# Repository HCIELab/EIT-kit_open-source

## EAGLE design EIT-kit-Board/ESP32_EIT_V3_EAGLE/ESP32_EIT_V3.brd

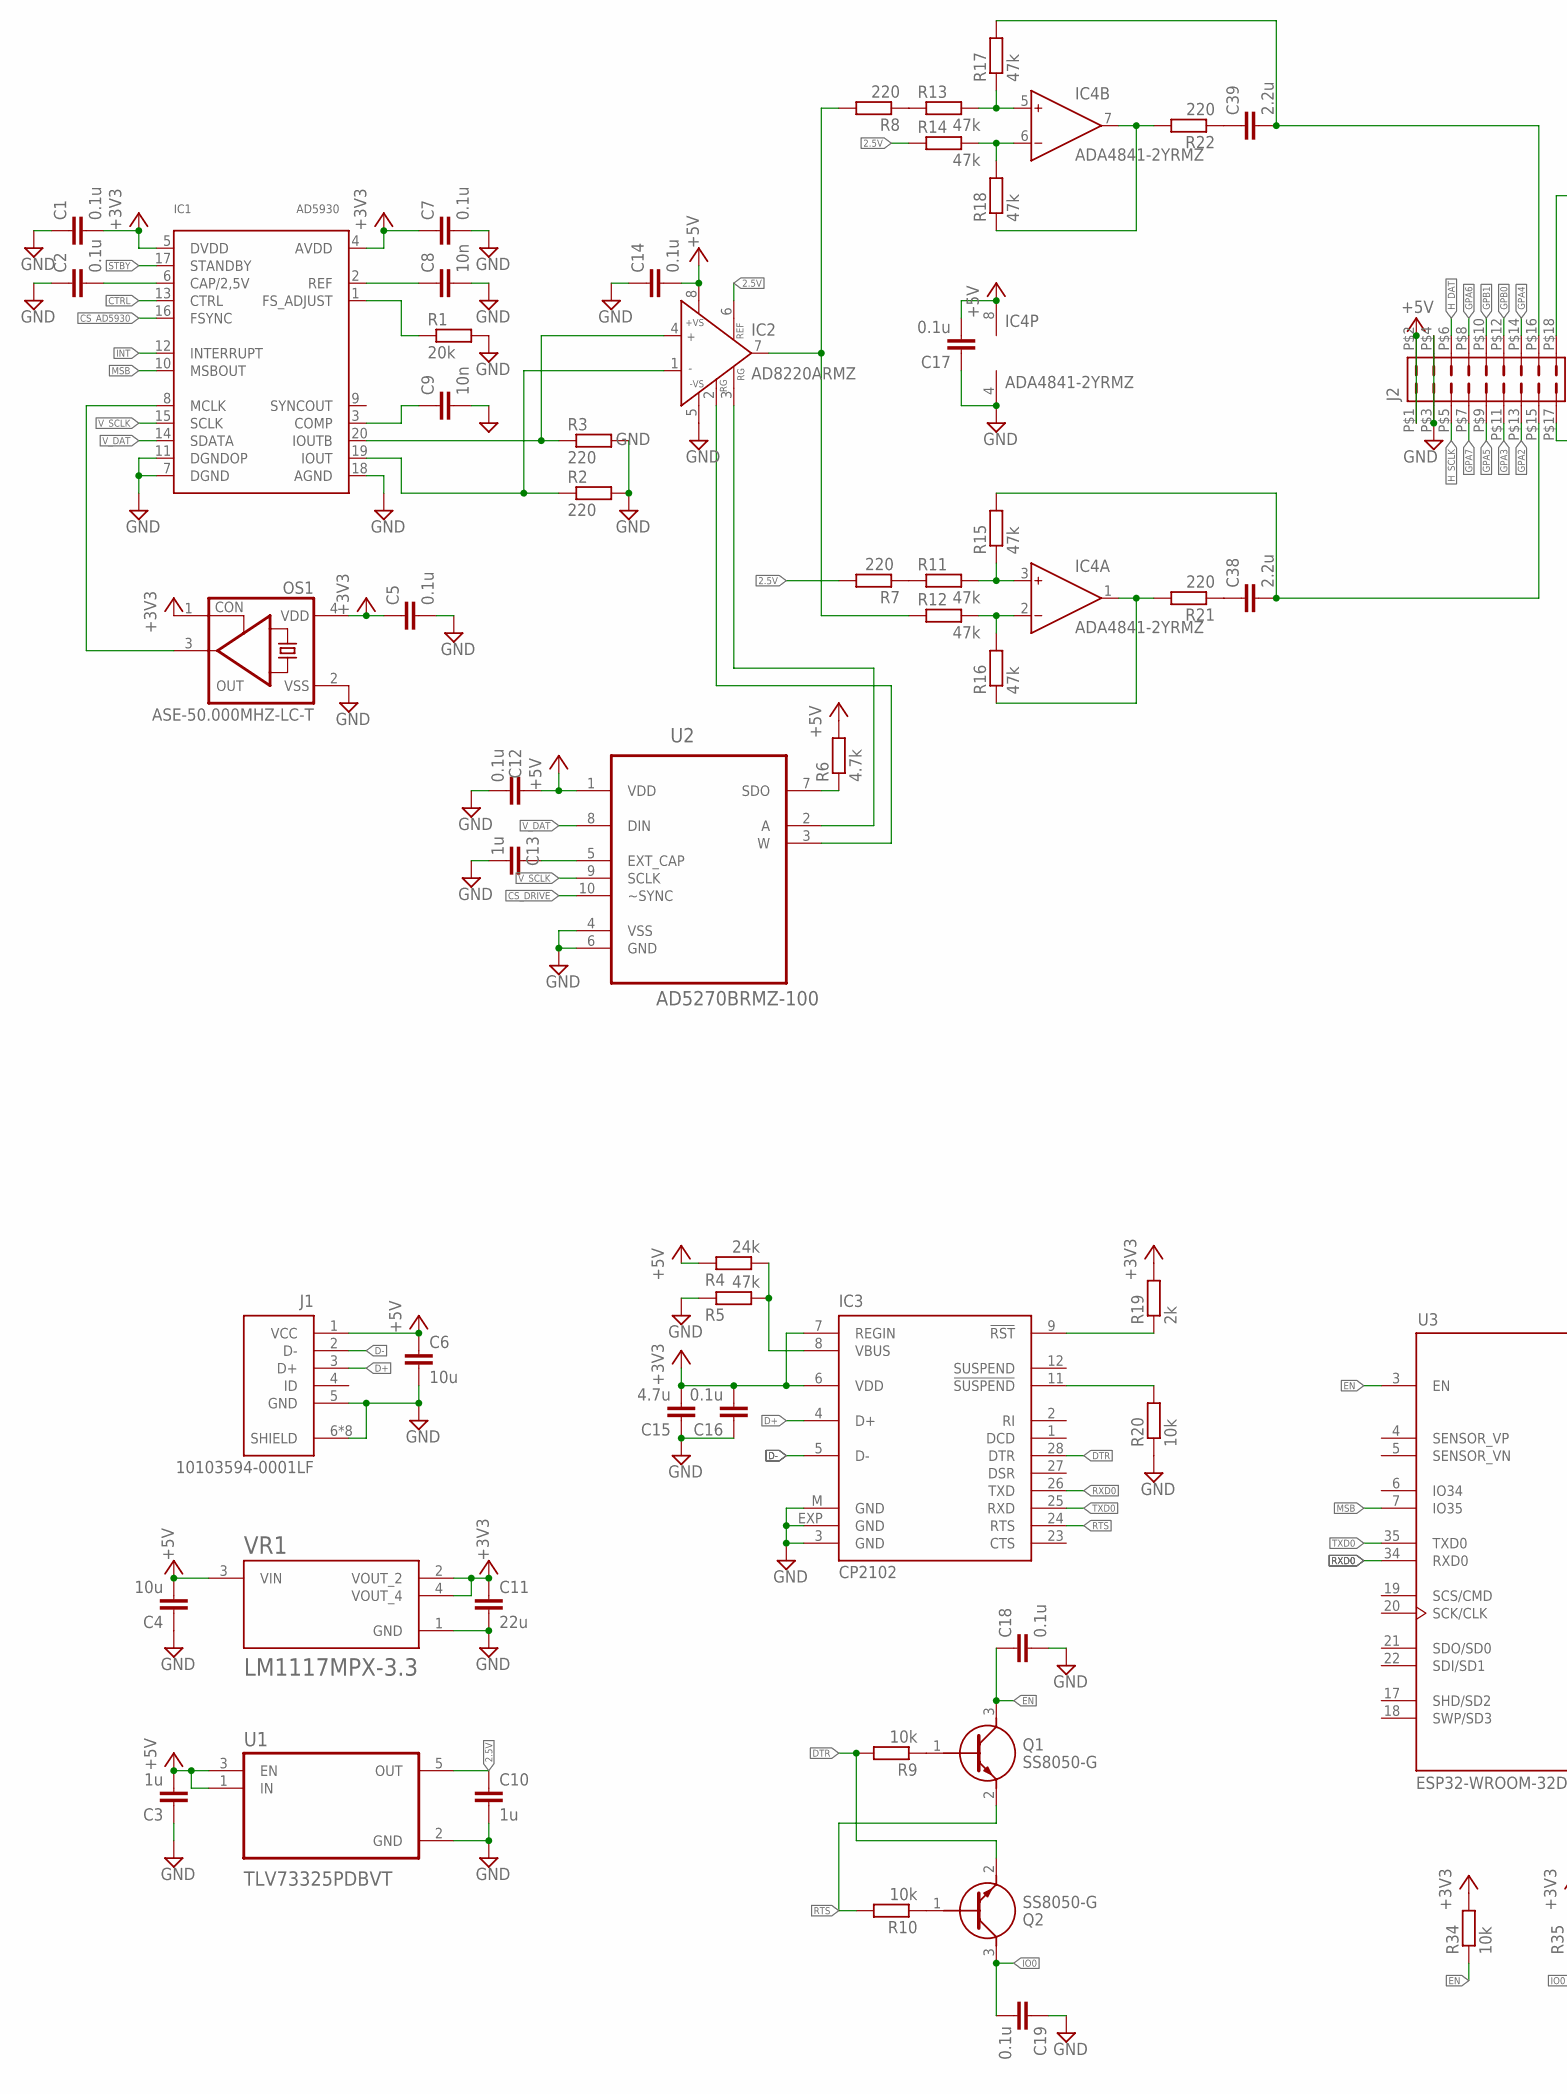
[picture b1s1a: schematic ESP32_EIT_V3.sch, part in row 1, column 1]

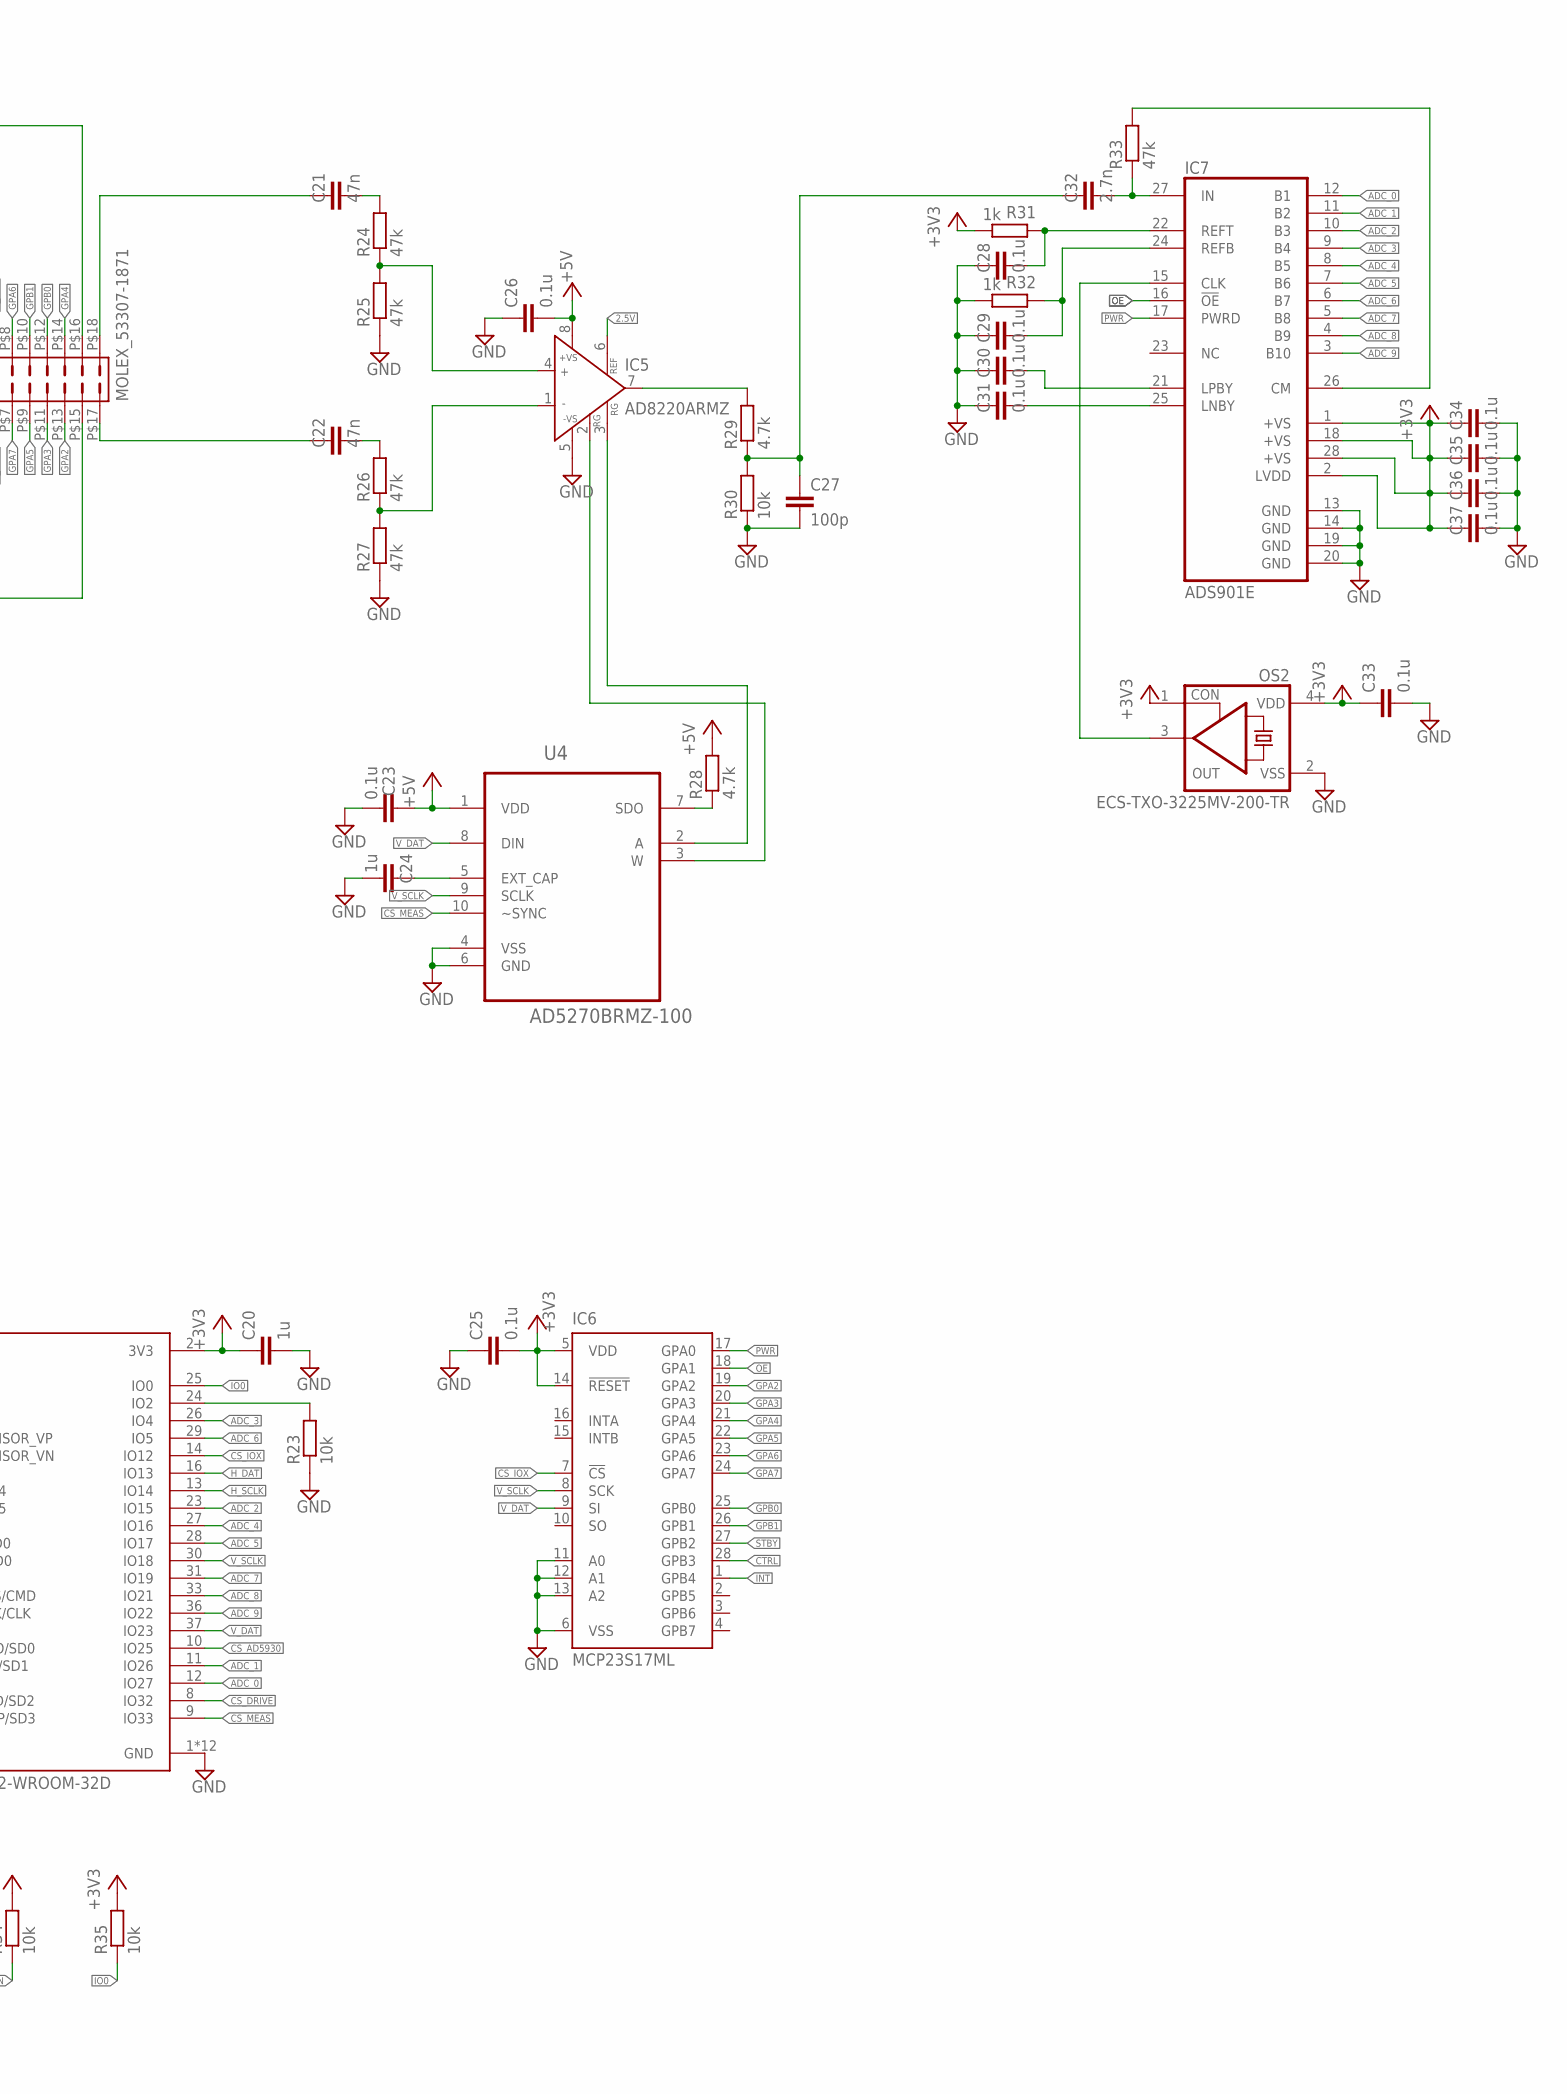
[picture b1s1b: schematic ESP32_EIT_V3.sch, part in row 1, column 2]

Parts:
C1, C2, C5, C7, C12, C14, C16, C17, C18, C19, C23, C25, C26, C28, C29, C30, C31, C33, C34, C35, C36, C37: 0.1u; C0603
C3, C10, C13, C20, C24: 1u; C0603
C4, C6: 10u; C0805
C8, C9: 10n; C0603
C11: 22u; C0805
C15: 4.7u; C0603
C21, C22: 47n; C0603
C27: 100p; C0603
C32: 2.7n; C0603
C38, C39: 2.2u; C0603
IC1: AD5930; TSSOP20
IC2, IC5: AD8220ARMZ; MSOP8
IC3: CP2102; MLP28
IC4: ADA4841-2YRMZ; MSOP8
IC6: MCP23S17ML; QFN28-ML_6X6MM
IC7: ADS901E; SSOP28BU
J1: 10103594-0001LF; AMPHENOL_10103594-0001LF
J2: MOLEX_53307-1871
OS1: ASE-50.000MHZ-LC-T; 2.5X2-4-PAD
OS2: ECS-TXO-3225MV-200-TR; 2.5X2-4-PAD
Q1, Q2: SS8050-G; SOT95P240X115-3N
R1: 20k; R0603
R2, R3, R7, R8, R21, R22: 220; R0603
R4: 24k; R0603
R5, R11, R12, R13, R14, R15, R16, R17, R18, R24, R25, R26, R27, R33: 47k; R0603
R6, R28, R29: 4.7k; R0603
R9, R10, R20, R23, R30, R34, R35: 10k; R0603
R19: 2k; R0603
R31, R32: 1k; R0603
U1: TLV73325PDBVT; SOT95P280X145-5N
U2, U4: AD5270BRMZ-100; SOP50P490X110-10N
U3: ESP32-WROOM-32D; MODULE_ESP32-WROOM-32D
VR1: LM1117MPX-3.3; VREG_LM1117MPX-3.3

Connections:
2.5V: C10.1, IC2.6 (REF), IC5.6 (REF), R7.2, R14.1, U1.5 (OUT)
+3V3: C1.2, C5.1, C7.1, C11.1, C15.2, C16.2, C20.1, C25.2, C33.1, C34.1, C35.1, C36.1, C37.1, IC1.4 (AVDD), IC1.5 (DVDD), IC3.6 (VDD), IC3.7 (REGIN), IC6.5 (VDD), IC6.14 (!RESET), IC7.1 (+VS), IC7.2 (LVDD), IC7.18 (+VS), IC7.28 (+VS), OS1.1 (CON), OS1.4 (VDD), OS2.1 (CON), OS2.4 (VDD), R19.2, R31.2, R34.2, R35.2, U3.2 (3V3), VR1.2 (VOUT_2), VR1.4 (VOUT_4)
+5V: C3.2, C4.2, C6.1, C12.1, C14.2, C17.2, C23.1, C26.2, IC2.8 (+VS), IC4.8 (V+), IC5.8 (+VS), J1.1 (VCC), J2.P$1 (1), J2.P$2 (2), R4.2, R6.2, R28.2, U1.1 (IN), U1.3 (EN), U2.1 (VDD), U4.1 (VDD), VR1.3 (VIN)
ADC_0: IC7.12 (B1), U3.12 (IO27)
ADC_1: IC7.11 (B2), U3.11 (IO26)
ADC_2: IC7.10 (B3), U3.23 (IO15)
ADC_3: IC7.9 (B4), U3.26 (IO4)
ADC_4: IC7.8 (B5), U3.27 (IO16)
ADC_5: IC7.7 (B6), U3.28 (IO17)
ADC_6: IC7.6 (B7), U3.29 (IO5)
ADC_7: IC7.5 (B8), U3.31 (IO19)
ADC_8: IC7.4 (B9), U3.33 (IO21)
ADC_9: IC7.3 (B10), U3.36 (IO22)
CS_AD5930: IC1.16 (FSYNC), U3.10 (IO25)
CS_DRIVE: U2.10 (~SYNC), U3.8 (IO32)
CS_IOX: IC6.7 (!CS), U3.14 (IO12)
CS_MEAS: U3.9 (IO33), U4.10 (~SYNC)
CTRL: IC1.13 (CTRL), IC6.28 (GPB3)
D+: IC3.4 (D+), J1.3 (D+)
D-: IC3.5 (D-), J1.2 (D-)
DTR: IC3.28 (DTR), Q2.2 (E), R9.2
EN: C18.1, Q1.3 (C), R34.1, U3.3 (EN)
GND: C1.1, C2.1, C3.1, C4.1, C5.2, C6.2, C7.2, C8.2, C9.2, C10.2, C11.2, C12.2, C13.2, C14.1, C15.1, C16.1, C17.1, C18.2, C19.1, C20.2, C23.2, C24.2, C25.1, C26.1, C27.2, C28.1, C29.1, C30.1, C31.1, C33.2, C34.2, C35.2, C36.2, C37.2, IC1.7 (DGND), IC1.11 (DGNDOP), IC1.18 (AGND), IC2.5 (-VS), IC3.3 (GND), IC3.EXP (GND), IC3.M (GND), IC4.4 (V-), IC5.5 (-VS), IC6.6 (VSS), IC6.11 (A0), IC6.12 (A1), IC6.13 (A2), IC7.13 (GND), IC7.14 (GND), IC7.19 (GND), IC7.20 (GND), J1.5 (GND), J1.6 (SHIELD), J1.7 (SHIELD), J1.8 (SHIELD), J1.9 (SHIELD), J1.10 (SHIELD), J1.11 (SHIELD), J1.S1 (SHIELD), J1.S2 (SHIELD), J2.P$3 (3), J2.P$4 (4), OS1.2 (VSS), OS2.2 (VSS), R1.2, R2.2, R3.2, R5.2, R20.1, R23.1, R25.1, R27.1, R30.1, R32.2, U1.2 (GND), U2.4 (VSS), U2.6 (GND), U3.1 (GND), U3.15 (GND), U3.38 (GND), U3.39_1 (GND), U3.39_2 (GND), U3.39_3 (GND), U3.39_4 (GND), U3.39_5 (GND), U3.39_6 (GND), U3.39_7 (GND), U3.39_8 (GND), U3.39_9 (GND), U4.4 (VSS), U4.6 (GND), VR1.1 (GND)
GPA2: IC6.19 (GPA2), J2.P$13 (13)
GPA3: IC6.20 (GPA3), J2.P$11 (11)
GPA4: IC6.21 (GPA4), J2.P$14 (14)
GPA5: IC6.22 (GPA5), J2.P$9 (9)
GPA6: IC6.23 (GPA6), J2.P$8 (8)
GPA7: IC6.24 (GPA7), J2.P$7 (7)
GPB0: IC6.25 (GPB0), J2.P$12 (12)
GPB1: IC6.26 (GPB1), J2.P$10 (10)
H_DAT: J2.P$6 (6), U3.16 (IO13)
H_SCLK: J2.P$5 (5), U3.13 (IO14)
INT: IC1.12 (INTERRUPT), IC6.1 (GPB4)
IO0: C19.2, Q2.3 (C), R35.1, U3.25 (IO0)
MSB: IC1.10 (MSBOUT), U3.7 (IO35)
unnamed: IC1.1 (FS_ADJUST), R1.1
unnamed: C8.1, IC1.2 (REF)
unnamed: C9.1, IC1.3 (COMP)
unnamed: IC1.20 (IOUTB), IC2.4 (IN+), R3.1
unnamed: R7.1, R11.1
unnamed: R8.1, R13.1
unnamed: IC4.6 (IN-), R14.2, R18.2
unnamed: IC4.5 (IN+), R13.2, R17.1
unnamed: IC4.3 (IN+), R11.2, R15.1
unnamed: IC4.2 (IN-), R12.2, R16.2
unnamed: IC4.1 (OUT), R16.1, R21.2
unnamed: IC1.8 (MCLK), OS1.3 (OUT)
unnamed: C2.2, IC1.6 (CAP/2,5V)
unnamed: IC4.7 (OUT), R18.1, R22.2
unnamed: R6.1, U2.7 (SDO)
unnamed: IC1.19 (IOUT), IC2.1 (IN-), R2.1
unnamed: IC2.2 (RG), U2.3 (W)
unnamed: IC2.7 (OUT), R8.2, R12.1
unnamed: IC2.3 (RG), U2.2 (A)
unnamed: C13.1, U2.5 (EXT_CAP)
unnamed: R28.1, U4.7 (SDO)
unnamed: IC7.26 (CM), R33.2
unnamed: C32.2, IC7.27 (IN), R33.1
unnamed: C24.1, U4.5 (EXT_CAP)
unnamed: C28.2, IC7.22 (REFT), R31.1
unnamed: C29.2, IC7.24 (REFB), R32.1
unnamed: C31.2, IC7.25 (LNBY)
unnamed: C30.2, IC7.21 (LPBY)
unnamed: IC5.2 (RG), U4.3 (W)
unnamed: IC7.15 (CLK), OS2.3 (OUT)
unnamed: IC5.7 (OUT), R29.2
unnamed: C21.2, R24.2
unnamed: IC5.4 (IN+), R24.1, R25.2
unnamed: IC5.1 (IN-), R26.1, R27.2
unnamed: C22.2, R26.2
unnamed: IC5.3 (RG), U4.2 (A)
unnamed: C27.1, C32.1, R29.1, R30.2
unnamed: IC3.11 (!SUSPEND), R20.2
unnamed: IC3.8 (VBUS), R4.1, R5.1
unnamed: R23.2, U3.24 (IO2)
unnamed: IC3.9 (!RST), R19.1
unnamed: Q1.1 (B), R9.1
unnamed: Q2.1 (B), R10.1
unnamed: C21.1, J2.P$18 (18)
unnamed: C22.1, J2.P$17 (17)
unnamed: C38.2, J2.P$15 (15), R15.2
unnamed: C39.2, J2.P$16 (16), R17.2
unnamed: C38.1, R21.1
unnamed: C39.1, R22.1
OE: IC6.18 (GPA1), IC7.16 (!OE)
PWR: IC6.17 (GPA0), IC7.17 (PWRD)
RTS: IC3.24 (RTS), Q1.2 (E), R10.2
RXD0: IC3.26 (TXD), U3.34 (RXD0)
STBY: IC1.17 (STANDBY), IC6.27 (GPB2)
TXD0: IC3.25 (RXD), U3.35 (TXD0)
V_DAT: IC1.14 (SDATA), IC6.9 (SI), U2.8 (DIN), U3.37 (IO23), U4.8 (DIN)
V_SCLK: IC1.15 (SCLK), IC6.8 (SCK), U2.9 (SCLK), U3.30 (IO18), U4.9 (SCLK)

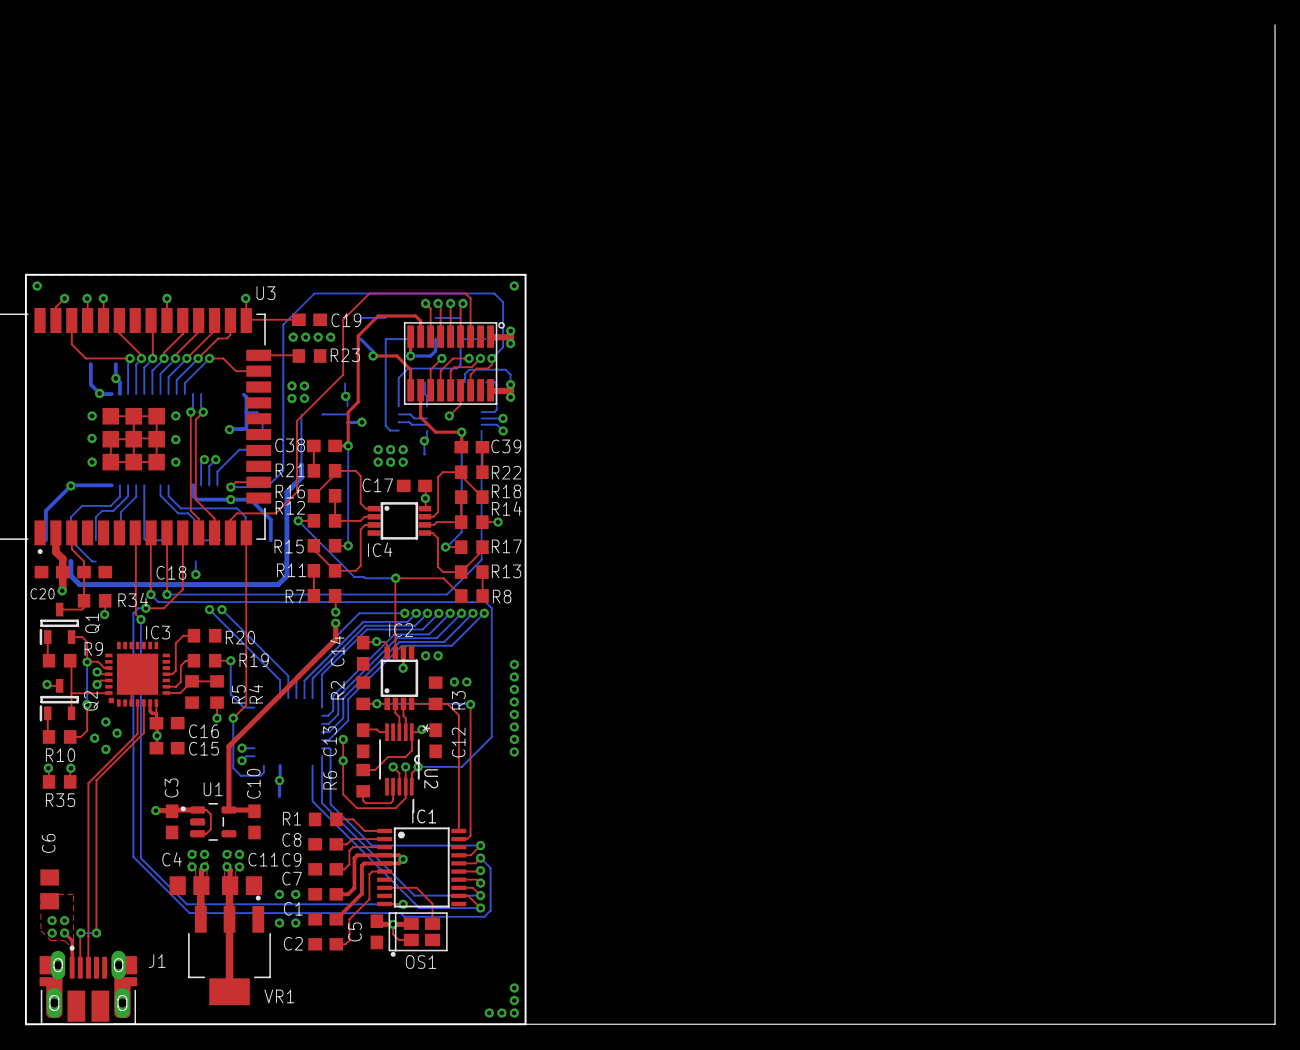
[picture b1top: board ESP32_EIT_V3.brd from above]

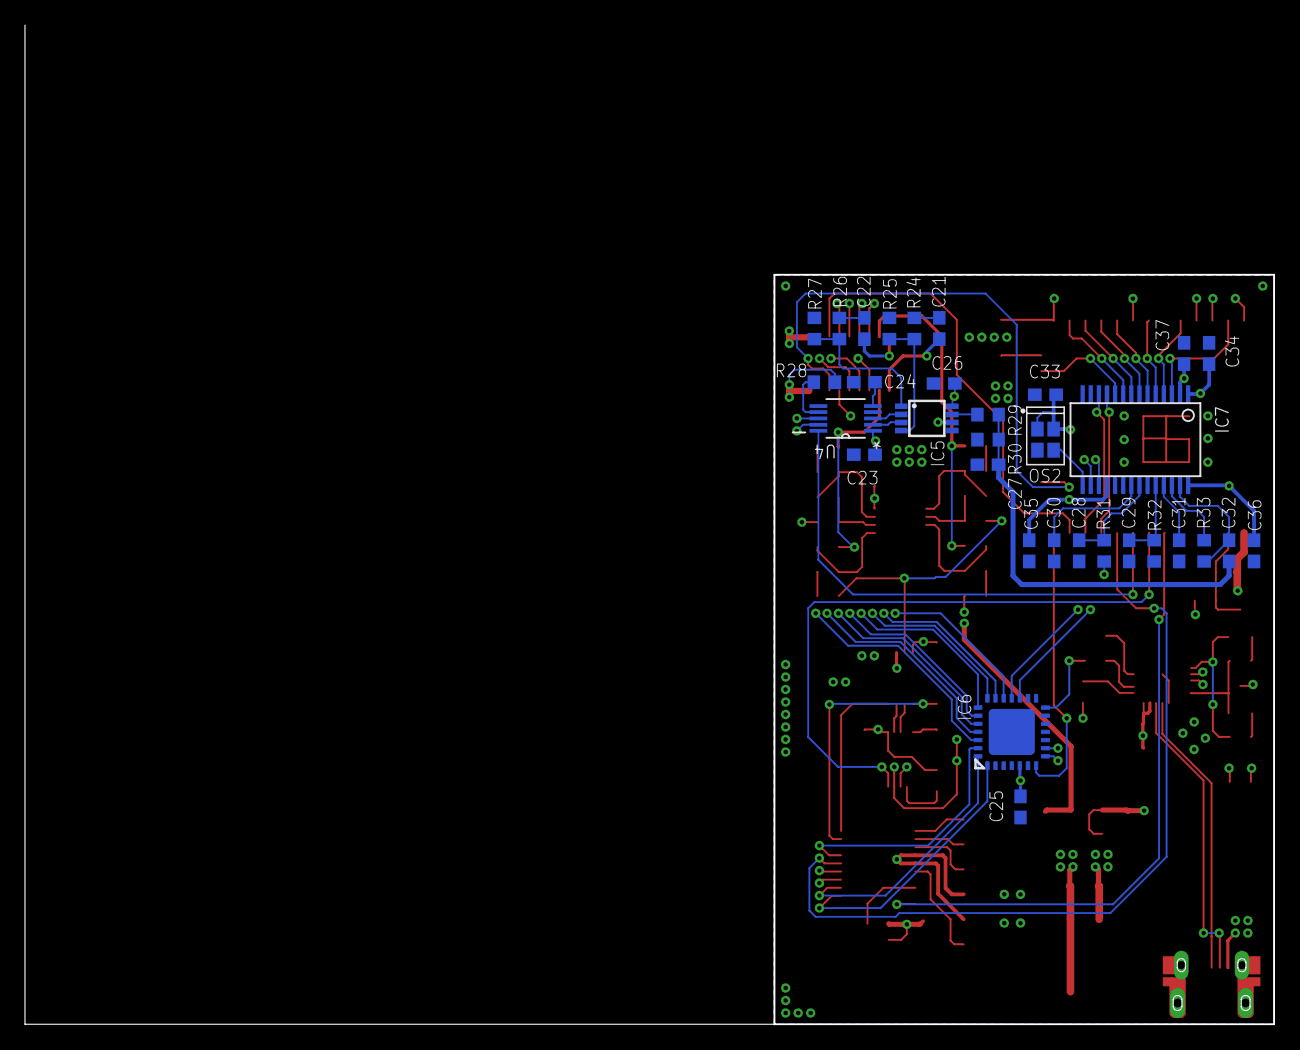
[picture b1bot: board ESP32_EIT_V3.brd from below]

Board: 4 copper layers, 40.0 x 60.0 mm, 92 parts (32 on the bottom side), 93 nets.

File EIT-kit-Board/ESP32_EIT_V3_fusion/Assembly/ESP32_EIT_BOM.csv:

Qty,Value,Device,Package,Parts,Description,
22,0.1u,C-EUC0603,C0603,"C1, C2, C5, C7, C12, C14, C16, C17, C18, C19, C23, C25, C26, C28, C29, C30, C31, C33, C34, C35, C36, C37","CAPACITOR, European symbol",
1,100p,C-EUC0603,C0603,C27,"CAPACITOR, European symbol",
1,10103594-0001LF,10103594-0001LF,AMPHENOL_10103594-0001LF,J1,"USB - micro B USB 2.0 Receptacle Connector 5 Position Surface Mount, Right Angle; Through Hole  Check prices",
7,10k,R-EU_R0603,R0603,"R9, R10, R20, R23, R30, R34, R35","RESISTOR, European symbol",
2,10n,C-EUC0603,C0603,"C8, C9","CAPACITOR, European symbol",
2,10u,C-EUC0805,C0805,"C4, C6","CAPACITOR, European symbol",
2,1k,R-EU_R0603,R0603,"R31, R32","RESISTOR, European symbol",
5,1u,C-EUC0603,C0603,"C3, C10, C13, C20, C24","CAPACITOR, European symbol",
2,2.2u,C-EUC0603,C0603,"C38, C39","CAPACITOR, European symbol",
1,2.7n,C-EUC0603,C0603,C32,"CAPACITOR, European symbol",
1,20k,R-EU_R0603,R0603,R1,"RESISTOR, European symbol",
6,220,R-EU_R0603,R0603,"R2, R3, R7, R8, R21, R22","RESISTOR, European symbol",
1,22u,C-EUC0805,C0805,C11,"CAPACITOR, European symbol",
1,24k,R-EU_R0603,R0603,R4,"RESISTOR, European symbol",
1,2k,R-EU_R0603,R0603,R19,"RESISTOR, European symbol",
3,4.7k,R-EU_R0603,R0603,"R6, R28, R29","RESISTOR, European symbol",
1,4.7u,C-EUC0603,C0603,C15,"CAPACITOR, European symbol",
14,47k,R-EU_R0603,R0603,"R5, R11, R12, R13, R14, R15, R16, R17, R18, R24, R25, R26, R27, R33","RESISTOR, European symbol",
2,47n,C-EUC0603,C0603,"C21, C22","CAPACITOR, European symbol",
2,AD5270BRMZ-100,AD5270BRMZ-100,SOP50P490X110-10N,"U2, U4","1024-/256-Position, 1% Resistor Tolerance Error, SPI Interface and 50-TP Memory Digital Rheostat  Check prices",
1,AD5930,AD5930,TSSOP20,IC1,"Programmable Waveform Generator",
2,AD8220ARMZ,AD8220ARMZ,MSOP8,"IC2, IC5","Single-Supply, Rail-to-Rail, Low Power, FET Input Op Amp",
1,ADA4841-2YRMZ,ADA4841-2YRMZ,MSOP8,IC4,"Ultralow Noise Amplifier at Lower Power",
1,ADS901E,ADS901E,SSOP28BU,IC7,"10-Bit, 20 MSPS ADC SE/Diff Inputs",
1,ASE-50.000MHZ-LC-T,OSC-OE-IQXO-793,2.5X2-4-PAD,OS1,"OSCILLATOR WITH OE",
1,CP2102,CP2102,MLP28,IC3,"Single-Chip USB to UART Bridge",
1,ECS-TXO-3225MV-200-TR,OSC-OE-IQXO-793,2.5X2-4-PAD,OS2,"OSCILLATOR WITH OE",
1,ESP32-WROOM-32D,ESP32-WROOM-32D,MODULE_ESP32-WROOM-32D,U3,"Bluetooth, WiFi 802.11b/g/n, Bluetooth v4.2 + EDR, Class 1, 2 and 3 Transceiver Module 2.4GHz ~ 2.5GHz Integrated, Trace Surface Mount Check prices",
1,LM1117MPX-3.3,LM1117MPX-3.3,VREG_LM1117MPX-3.3,VR1,"800-mA 15-V linear voltage regulator 4-SOT-223 0 to 125  Check prices",
1,MCP23S17ML,MCP23S17ML,QFN28-ML_6X6MM,IC6,http://ww1.microchip.com/downloads/en/DeviceDoc/21952a.pdf,
1,MOLEX_53307-1871,MOLEX_53307-1871,MOLEX_53307-1871,J2,,
2,SS8050-G,SS8050-G,SOT95P240X115-3N,"Q1, Q2","Bipolar Transistors - BJT NPN TRANSISTOR 1.5A 40V",
1,TLV73325PDBVT,TLV73325PDBVT,SOT95P280X145-5N,U1,"Check prices",

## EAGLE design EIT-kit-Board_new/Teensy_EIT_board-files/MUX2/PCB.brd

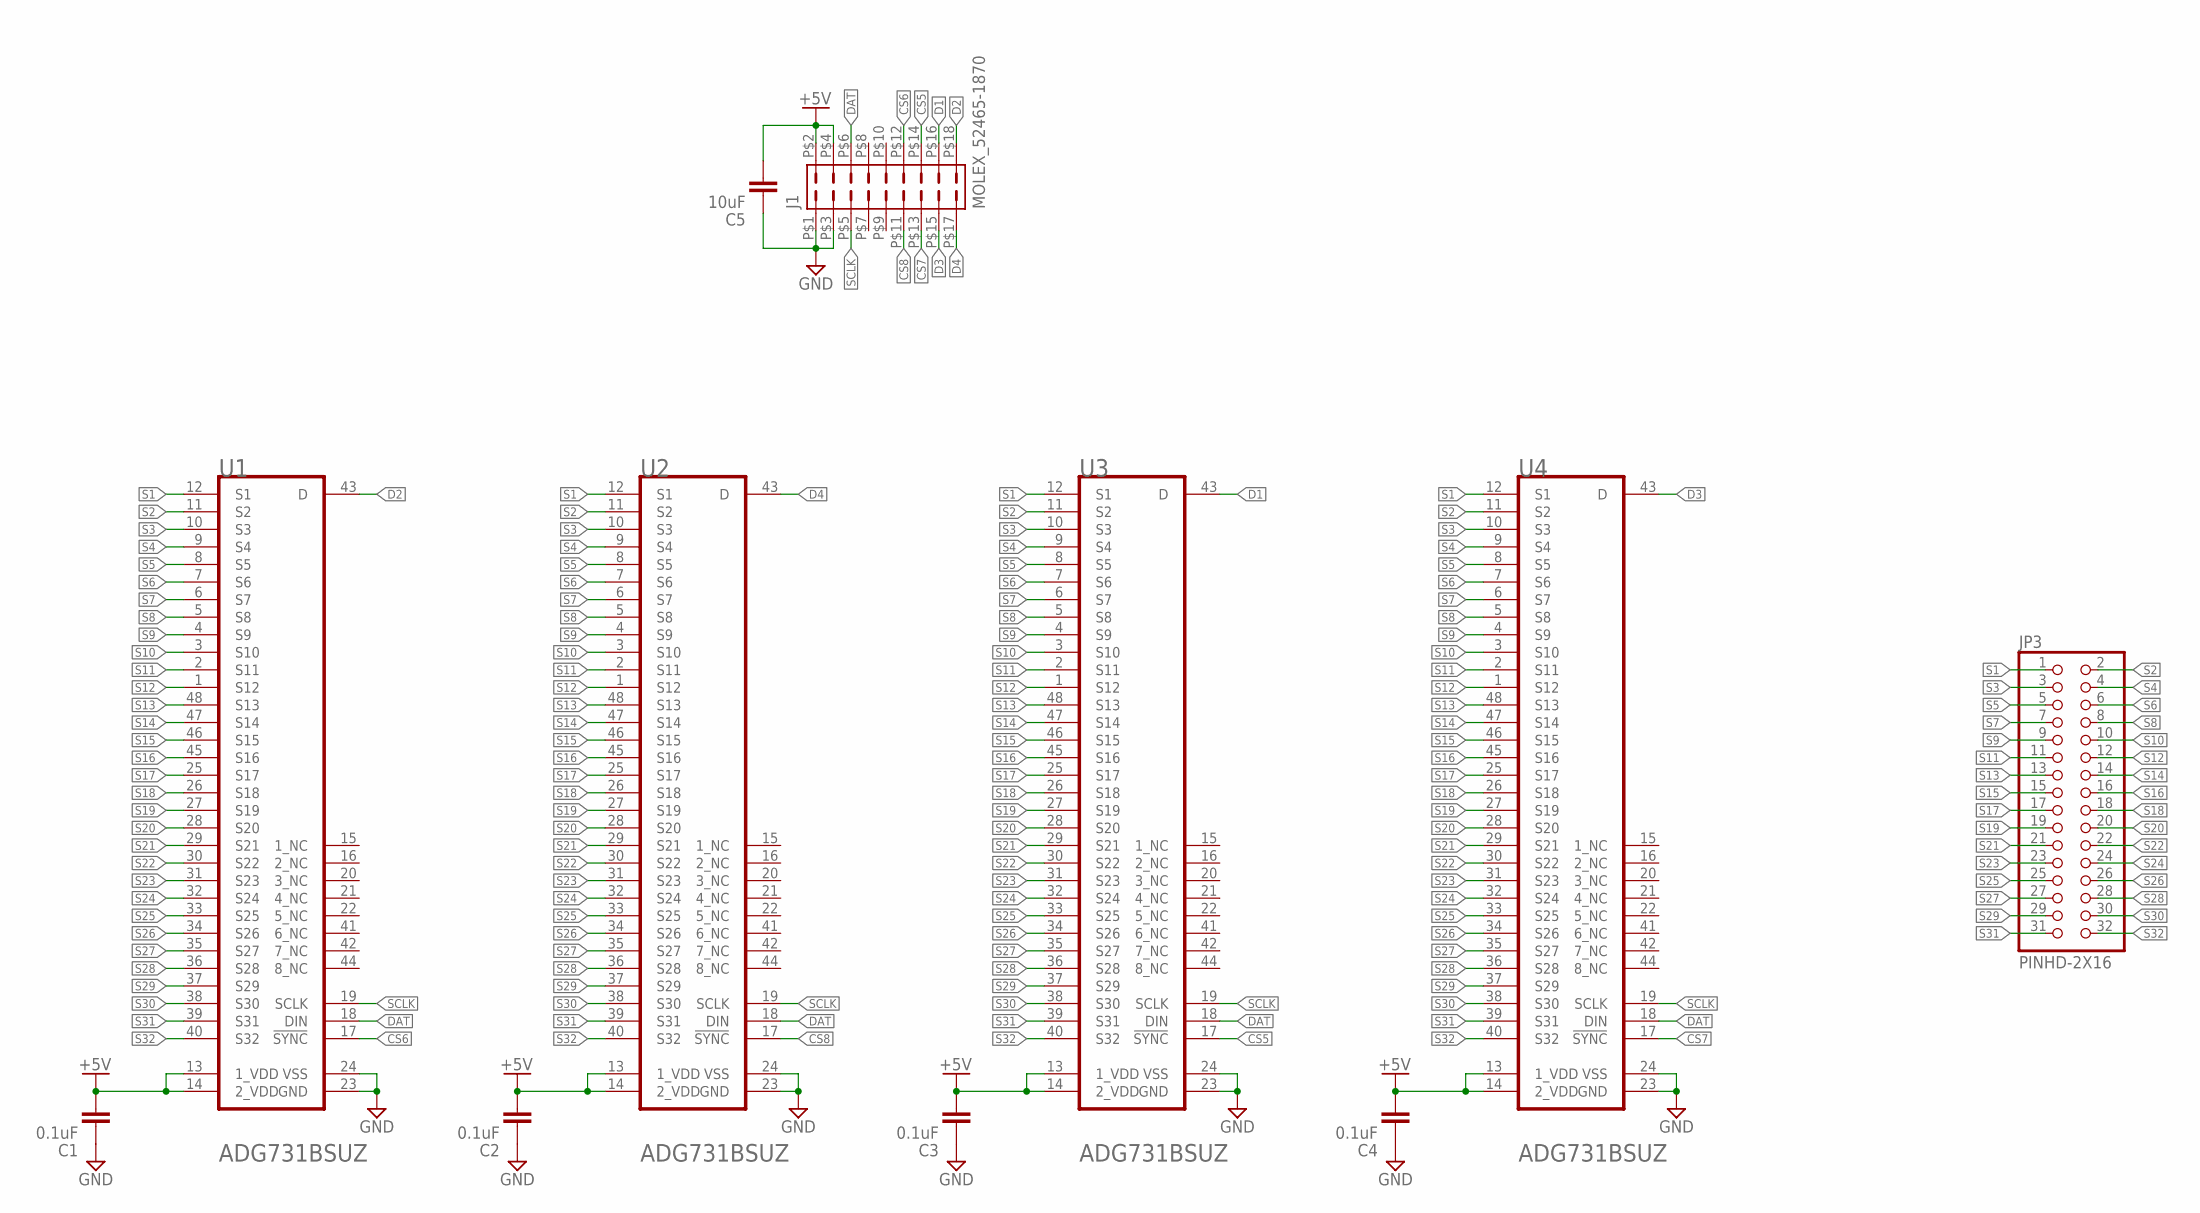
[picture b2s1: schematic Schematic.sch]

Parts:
C1, C2, C3, C4: 0.1uF; CAPC1608X85
C5: 10uF; CAPC2012X110
J1: MOLEX_52465-1870
JP3: PINHD-2X16; 2X16
U1, U2, U3, U4: ANALOG_DEVICES_ADG731BSUZANALOG_DEVICES_ADG731BSU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; ANALOG_DEVICES_ADG731BSUZ_0

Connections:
+5V: C1.2, C2.2, C3.2, C4.2, C5.2, J1.P$2 (2), J1.P$4 (4), U1.13 (1_VDD), U1.14 (2_VDD), U2.13 (1_VDD), U2.14 (2_VDD), U3.13 (1_VDD), U3.14 (2_VDD), U4.13 (1_VDD), U4.14 (2_VDD)
CS5: J1.P$14 (14), U3.17 (!SYNC!)
CS6: J1.P$12 (12), U1.17 (!SYNC!)
CS7: J1.P$13 (13), U4.17 (!SYNC!)
CS8: J1.P$11 (11), U2.17 (!SYNC!)
D1: J1.P$16 (16), U3.43 (D)
D2: J1.P$18 (18), U1.43 (D)
D3: J1.P$15 (15), U4.43 (D)
D4: J1.P$17 (17), U2.43 (D)
DAT: J1.P$6 (6), U1.18 (DIN), U2.18 (DIN), U3.18 (DIN), U4.18 (DIN)
GND: C1.1, C2.1, C3.1, C4.1, C5.1, J1.P$1 (1), J1.P$3 (3), U1.23 (GND), U1.24 (VSS), U2.23 (GND), U2.24 (VSS), U3.23 (GND), U3.24 (VSS), U4.23 (GND), U4.24 (VSS)
S1: JP3.1, U1.12 (S1), U2.12 (S1), U3.12 (S1), U4.12 (S1)
S2: JP3.2, U1.11 (S2), U2.11 (S2), U3.11 (S2), U4.11 (S2)
S3: JP3.3, U1.10 (S3), U2.10 (S3), U3.10 (S3), U4.10 (S3)
S4: JP3.4, U1.9 (S4), U2.9 (S4), U3.9 (S4), U4.9 (S4)
S5: JP3.5, U1.8 (S5), U2.8 (S5), U3.8 (S5), U4.8 (S5)
S6: JP3.6, U1.7 (S6), U2.7 (S6), U3.7 (S6), U4.7 (S6)
S7: JP3.7, U1.6 (S7), U2.6 (S7), U3.6 (S7), U4.6 (S7)
S8: JP3.8, U1.5 (S8), U2.5 (S8), U3.5 (S8), U4.5 (S8)
S9: JP3.9, U1.4 (S9), U2.4 (S9), U3.4 (S9), U4.4 (S9)
S10: JP3.10, U1.3 (S10), U2.3 (S10), U3.3 (S10), U4.3 (S10)
S11: JP3.11, U1.2 (S11), U2.2 (S11), U3.2 (S11), U4.2 (S11)
S12: JP3.12, U1.1 (S12), U2.1 (S12), U3.1 (S12), U4.1 (S12)
S13: JP3.13, U1.48 (S13), U2.48 (S13), U3.48 (S13), U4.48 (S13)
S14: JP3.14, U1.47 (S14), U2.47 (S14), U3.47 (S14), U4.47 (S14)
S15: JP3.15, U1.46 (S15), U2.46 (S15), U3.46 (S15), U4.46 (S15)
S16: JP3.16, U1.45 (S16), U2.45 (S16), U3.45 (S16), U4.45 (S16)
S17: JP3.17, U1.25 (S17), U2.25 (S17), U3.25 (S17), U4.25 (S17)
S18: JP3.18, U1.26 (S18), U2.26 (S18), U3.26 (S18), U4.26 (S18)
S19: JP3.19, U1.27 (S19), U2.27 (S19), U3.27 (S19), U4.27 (S19)
S20: JP3.20, U1.28 (S20), U2.28 (S20), U3.28 (S20), U4.28 (S20)
S21: JP3.21, U1.29 (S21), U2.29 (S21), U3.29 (S21), U4.29 (S21)
S22: JP3.22, U1.30 (S22), U2.30 (S22), U3.30 (S22), U4.30 (S22)
S23: JP3.23, U1.31 (S23), U2.31 (S23), U3.31 (S23), U4.31 (S23)
S24: JP3.24, U1.32 (S24), U2.32 (S24), U3.32 (S24), U4.32 (S24)
S25: JP3.25, U1.33 (S25), U2.33 (S25), U3.33 (S25), U4.33 (S25)
S26: JP3.26, U1.34 (S26), U2.34 (S26), U3.34 (S26), U4.34 (S26)
S27: JP3.27, U1.35 (S27), U2.35 (S27), U3.35 (S27), U4.35 (S27)
S28: JP3.28, U1.36 (S28), U2.36 (S28), U3.36 (S28), U4.36 (S28)
S29: JP3.29, U1.37 (S29), U2.37 (S29), U3.37 (S29), U4.37 (S29)
S30: JP3.30, U1.38 (S30), U2.38 (S30), U3.38 (S30), U4.38 (S30)
S31: JP3.31, U1.39 (S31), U2.39 (S31), U3.39 (S31), U4.39 (S31)
S32: JP3.32, U1.40 (S32), U2.40 (S32), U3.40 (S32), U4.40 (S32)
SCLK: J1.P$5 (5), U1.19 (SCLK), U2.19 (SCLK), U3.19 (SCLK), U4.19 (SCLK)

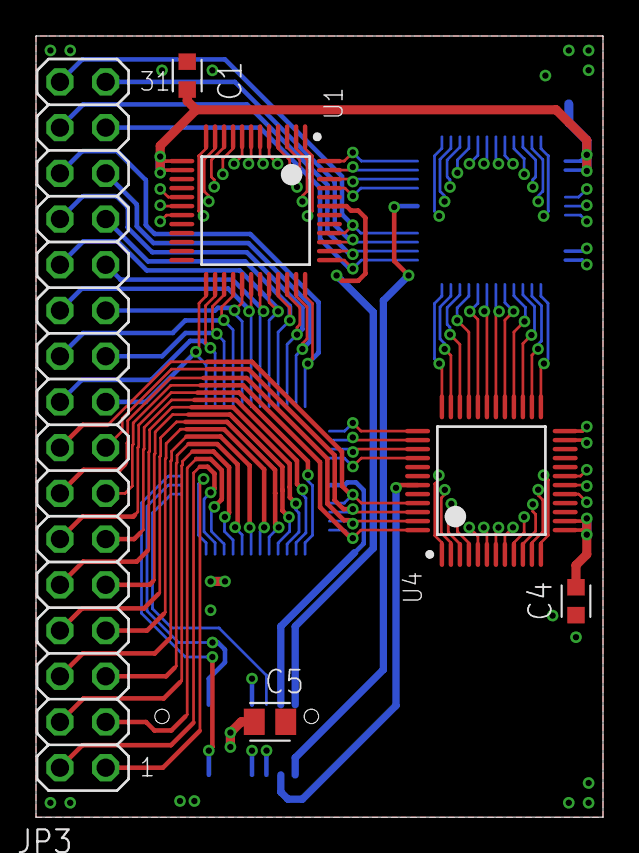
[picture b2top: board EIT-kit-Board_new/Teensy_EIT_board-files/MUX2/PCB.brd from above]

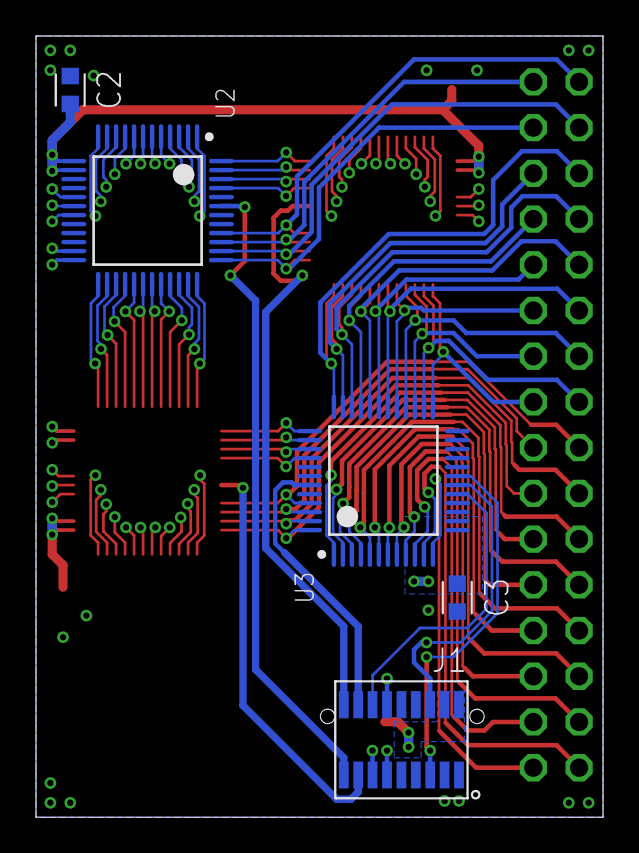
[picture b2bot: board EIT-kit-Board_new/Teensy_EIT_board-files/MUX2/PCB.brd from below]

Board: 4 copper layers, 31.5 x 43.4 mm, 11 parts (5 on the bottom side), 44 nets.

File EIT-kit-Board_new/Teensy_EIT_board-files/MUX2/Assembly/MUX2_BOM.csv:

Qty,Value,Device,Package,Parts,Description
4,0.1uF,C_CHIP-0603(1608-METRIC),CAPC1608X85,"C1, C2, C3, C4",Capacitor - Generic
1,10uF,C_CHIP-0805(2012-METRIC),CAPC2012X110,C5,Capacitor - Generic
4,ANALOG_DEVICES_ADG731BSUZANALOG_DEVICES_ADG731BSUZ_0_0,ANALOG_DEVICES_ADG731BSUZANALOG_DEVICES_ADG731BSUZ_0_0,TQFP-48,"U1, U2, U3, U4",ADI-ADG731-SU-48
1,MOLEX_52465-1870,MOLEX_52465-1870,MOLEX_52465-1870,J1,
1,PINHD-2X16,PINHD-2X16,2X16,JP3,"PIN HEADER 0.1"" PITCH"
